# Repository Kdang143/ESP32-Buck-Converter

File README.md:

# ESP32-Buck-Converter
Implemented in Ryerson's Robotics Club Rover to efficiently convert high voltage to low voltage.

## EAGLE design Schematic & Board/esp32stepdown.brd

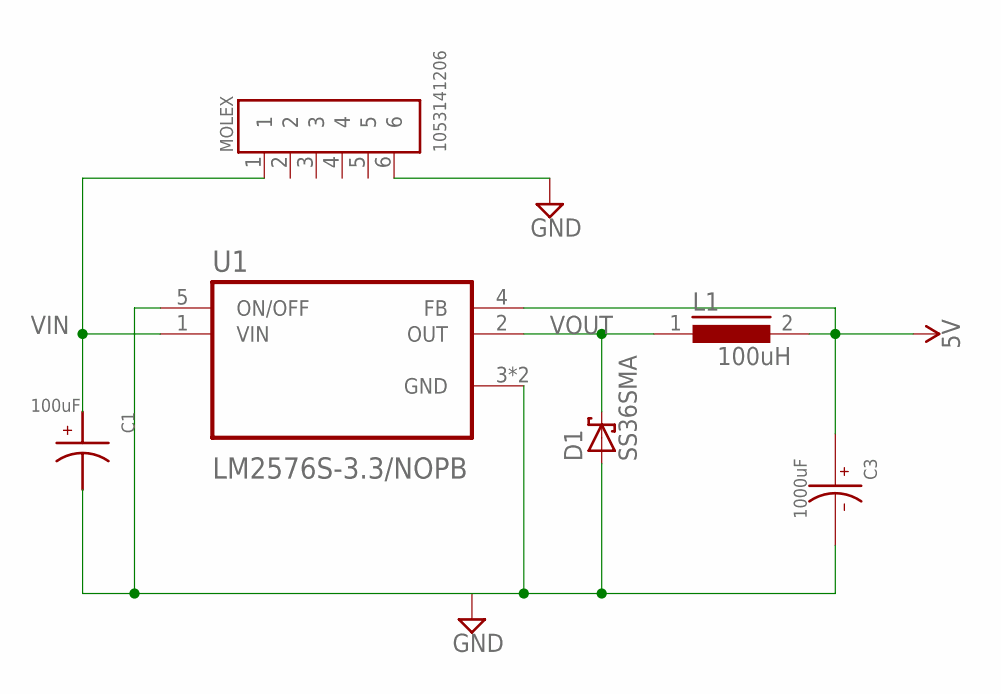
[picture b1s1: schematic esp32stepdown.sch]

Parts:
C1: 100uF; CAPPRD350W60D850H1250
C3: 1000uF; CAPPRD500W60D1000H2000B
D1: SS36SMA; SMA
L1: 100uH; DR73
MOLEX: 1053141206; MOLEX_1053141206
U1: LM2576S-3.3/NOPB; VREG_TPS79625KTTR

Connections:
GND: MOLEX.6
VIN: C1.1, MOLEX.1, U1.1 (VIN)
VOUT: C1.2, C3.+, C3.-, D1.A, D1.C, L1.1, L1.2, U1.2 (OUT), U1.3 (GND), U1.4 (FB), U1.5 (ON/OFF), U1.6 (GND)

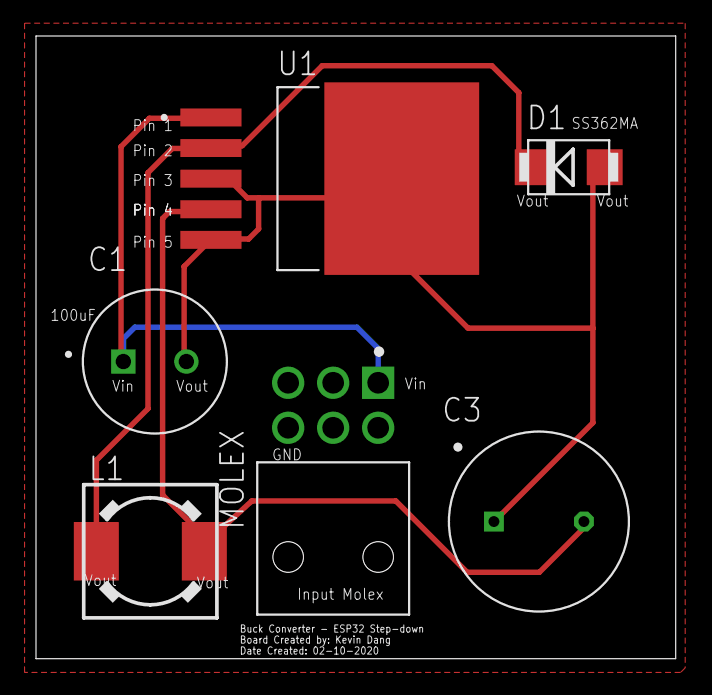
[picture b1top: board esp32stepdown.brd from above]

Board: 2 copper layers, 35.5 x 34.6 mm, 6 parts (0 on the bottom side), 2 nets.

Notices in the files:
parts and their libraries:
SparkFun-PowerSymbols: Licensing: Creative Commons ShareAlike 4.0 International - https://creativecommons.org/licenses/by-sa/4.0
